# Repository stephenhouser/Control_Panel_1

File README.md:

# Control Panel

The old-school hard-switch control panel for Home Automation.

This project has a few parts, each documented in their own section below.

- Project Box from Amazon; link and description
- Base and Top panels; SVG files for a laser cutter
- PCBs for Base and Top panels; KiCad PCB designs for manufacture

# Project Box

The project box is a [BUD Industries PC-11495 Plastic Style F Box 9" W x 5" H x 8.5" D, Natural](
https://www.amazon.com/gp/product/B005T98PQS/ref=ppx_yo_dt_b_search_asin_title?ie=UTF8&psc=1) which I found on Amazon for ~$32 USD. The [Dimensions](https://www.budind.com/wp-content/uploads/2019/01/hb11495.pdf) are available from BUD Industries (thank you!)

Another option, without the top display is the [BUD Industries PC-11493 Plastic Style F Box 9" L x 8.5" W x 1.98" H, Natural](https://www.amazon.com/gp/product/B005T592P0/ref=ppx_yo_dt_b_search_asin_title?ie=UTF8&psc=1) for ~$30 USD. The [Dimensions](https://www.budind.com/wp-content/uploads/2019/01/hb11493.pdf) are available from BUD Industries (thank you!)

You can find details on these boxes in general from [BUD Industries](https://www.budind.com/series/general-use-boxes/plasticase-style-f-plastic-cases-2/#group=series-products&external_dimensions_group=0&internal_dimensions=0)

# Base and Top Panels

Look in the Box_Panels directory. These are SVG files for a laser cutter

# PCBs for Base and Top panels

Uses KiCad v7.x for two PCB's; Control Board and Display Board.

Control Board
---

- Version 1.0 sent to fab on 7/17/2023

Components:

-  1 x ESP32 DevKit C ([Amazon](https://www.amazon.com/AITRIP-ESP32-DevKitC-Development-ESP32-WROOM-32D-Compatible/dp/B08HMJ1X6W/ref=sr_1_1_sspa?crid=38RBRSP8DY486&keywords=esp32+devkitc&qid=1689705861&sprefix=esp32+devkit+%2Caps%2C108&sr=8-1-spons&sp_csd=d2lkZ2V0TmFtZT1zcF9hdGY&psc=1))
- 16 x Addressable RGB LEDs ([sparkfun](https://www.sparkfun.com/products/12986))
- 10 x 2-position SPST Toggle Switches ([Amazon](https://www.amazon.com/MTS-101-Position-Miniature-Toggle-Switch/dp/B0799LBFNY/ref=sr_1_1_sspa?crid=Q083CMZJXX9C&keywords=mini+toggle+switch&qid=1689705831&sprefix=mini+toggle+switch%2Caps%2C114&sr=8-1-spons&sp_csd=d2lkZ2V0TmFtZT1zcF9hdGY&psc=1))
-  1 x 3-position SPST Toggle Switch ([Amazon](https://www.amazon.com/Twidec-Momentary-Miniature-Waterproof-MTS-123-MZ/dp/B07VHCB1Q4/ref=sr_1_4?crid=1ODFBUY13M4Y&keywords=3+position+mini+toggle+switch&qid=1689705803&sprefix=3+position+mini+toggle+switch%2Caps%2C120&sr=8-4))
- 10 x 1N4148 Diodes
-  1 x Rotary Encoder + Knob ([Amazon](https://www.amazon.com/gp/product/B07DM2YMT4/ref=ppx_yo_dt_b_search_asin_title?ie=UTF8&psc=1))
-  1 x Mini pushbutton switch ([Amazon](https://www.amazon.com/Momentary-Spring-Return-Self-Return-Pushbutton-Switches/dp/B09DJY5Y5L/ref=sr_1_3?keywords=mini+pushbutton+switch&qid=1689705893&sprefix=mini+pushbutton+s%2Caps%2C102&sr=8-3))

)
)

Display Board
---
Display Board not yet created.

Components:

-  2 x 0.56" LED Display Digital Tube Clock Module 4 Digit ([Amazon](https://www.amazon.com/gp/product/B0BB72R6RW/ref=ppx_yo_dt_b_asin_title_o03_s00?ie=UTF8&psc=1))

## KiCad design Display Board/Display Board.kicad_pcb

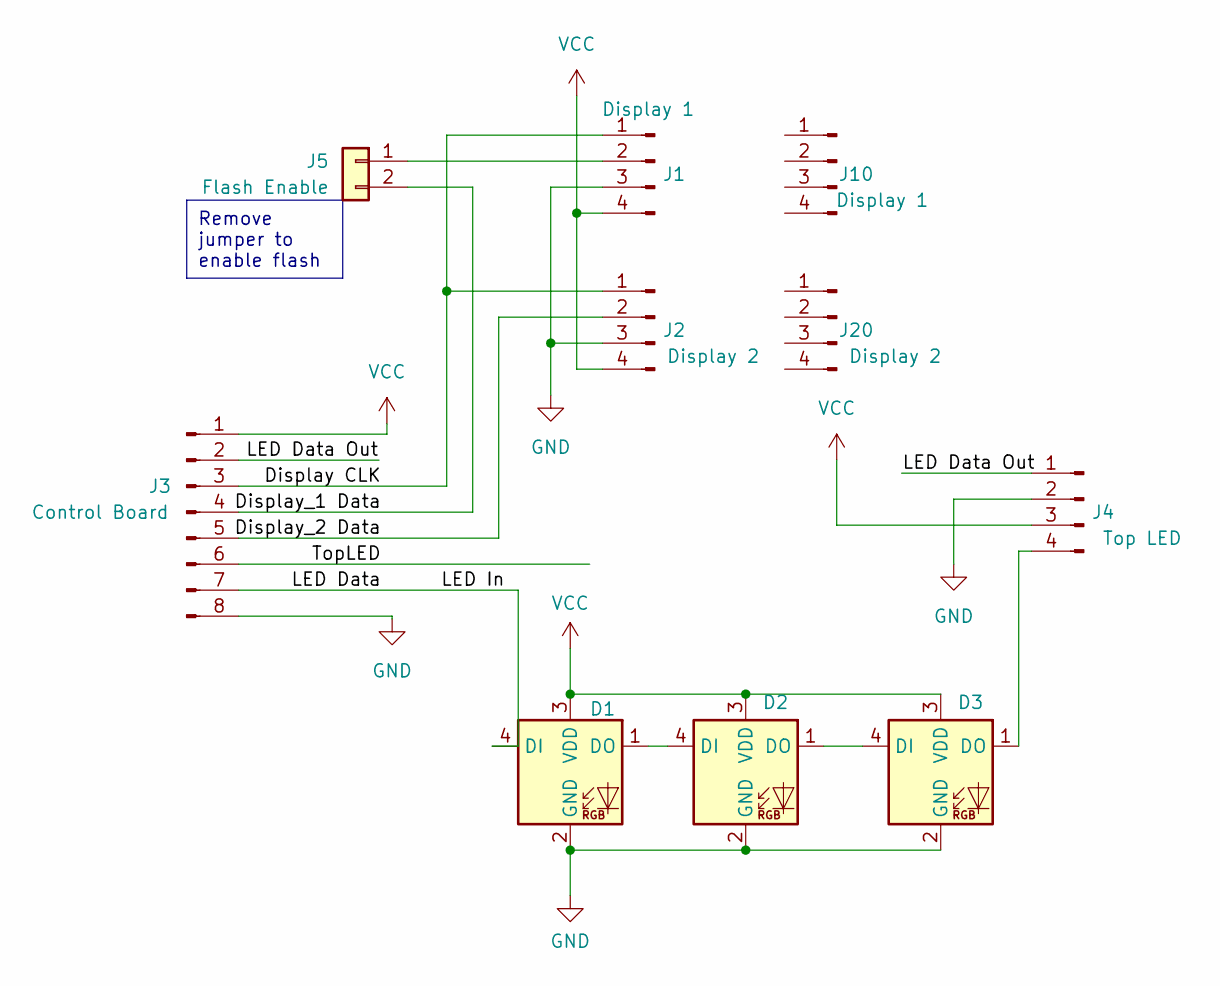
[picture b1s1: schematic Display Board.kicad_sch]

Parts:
D1, D2, D3: APA-106-F5; LED_D5.0mm-4_RGB
J1, J10: Display 1; PinHeader_1x04_P2.54mm_Vertical
J2, J20: Display 2; PinHeader_1x04_P2.54mm_Vertical
J3: Control Board; PinHeader_1x08_P2.00mm_Vertical
J4: Top LED; PinHeader_1x04_P2.00mm_Vertical
J5: Flash Enable; PinHeader_1x02_P2.54mm_Vertical

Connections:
/Display CLK: J1.1, J2.1, J3.3
/Display_1 Data: J3.4, J5.2
/Display_2 Data: J2.2, J3.5
/LED Data: D1.4 (DI), J3.7
/LED Data Out: J3.2, J4.1
/TopLED: J3.6
GND: D1.2 (GND), D2.2 (GND), D3.2 (GND), J1.3, J2.3, J3.8, J4.2
unnamed: D1.1 (DO), D2.4 (DI)
unnamed: D2.1 (DO), D3.4 (DI)
unnamed: D3.1 (DO), J4.4
unnamed: J1.2, J5.1
VCC: D1.3 (VDD), D2.3 (VDD), D3.3 (VDD), J1.4, J2.4, J3.1, J4.3

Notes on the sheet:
Remove jumper to enable flash

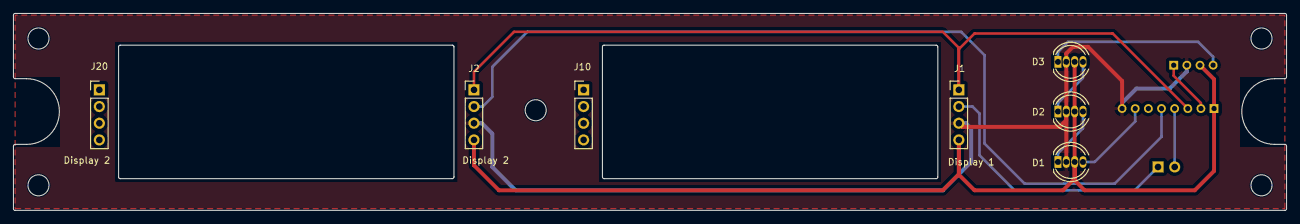
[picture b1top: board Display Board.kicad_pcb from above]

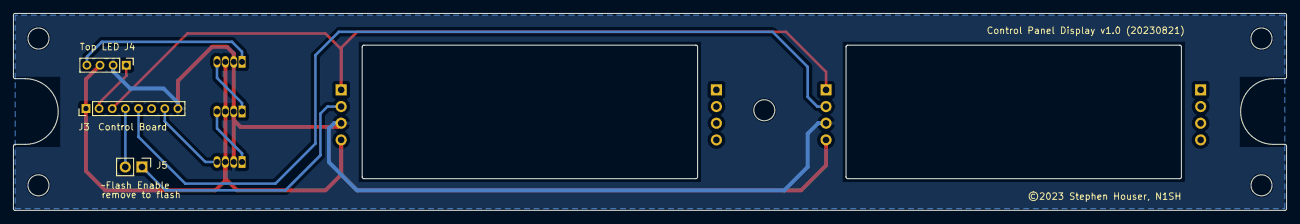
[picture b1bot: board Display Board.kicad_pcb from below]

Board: 2 copper layers, 193.8 x 30.0 mm, 15 parts (3 on the bottom side), 11 nets.

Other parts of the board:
REF01, REF02, REF03, REF04, REF05: MountingHole_3.2mm_M3

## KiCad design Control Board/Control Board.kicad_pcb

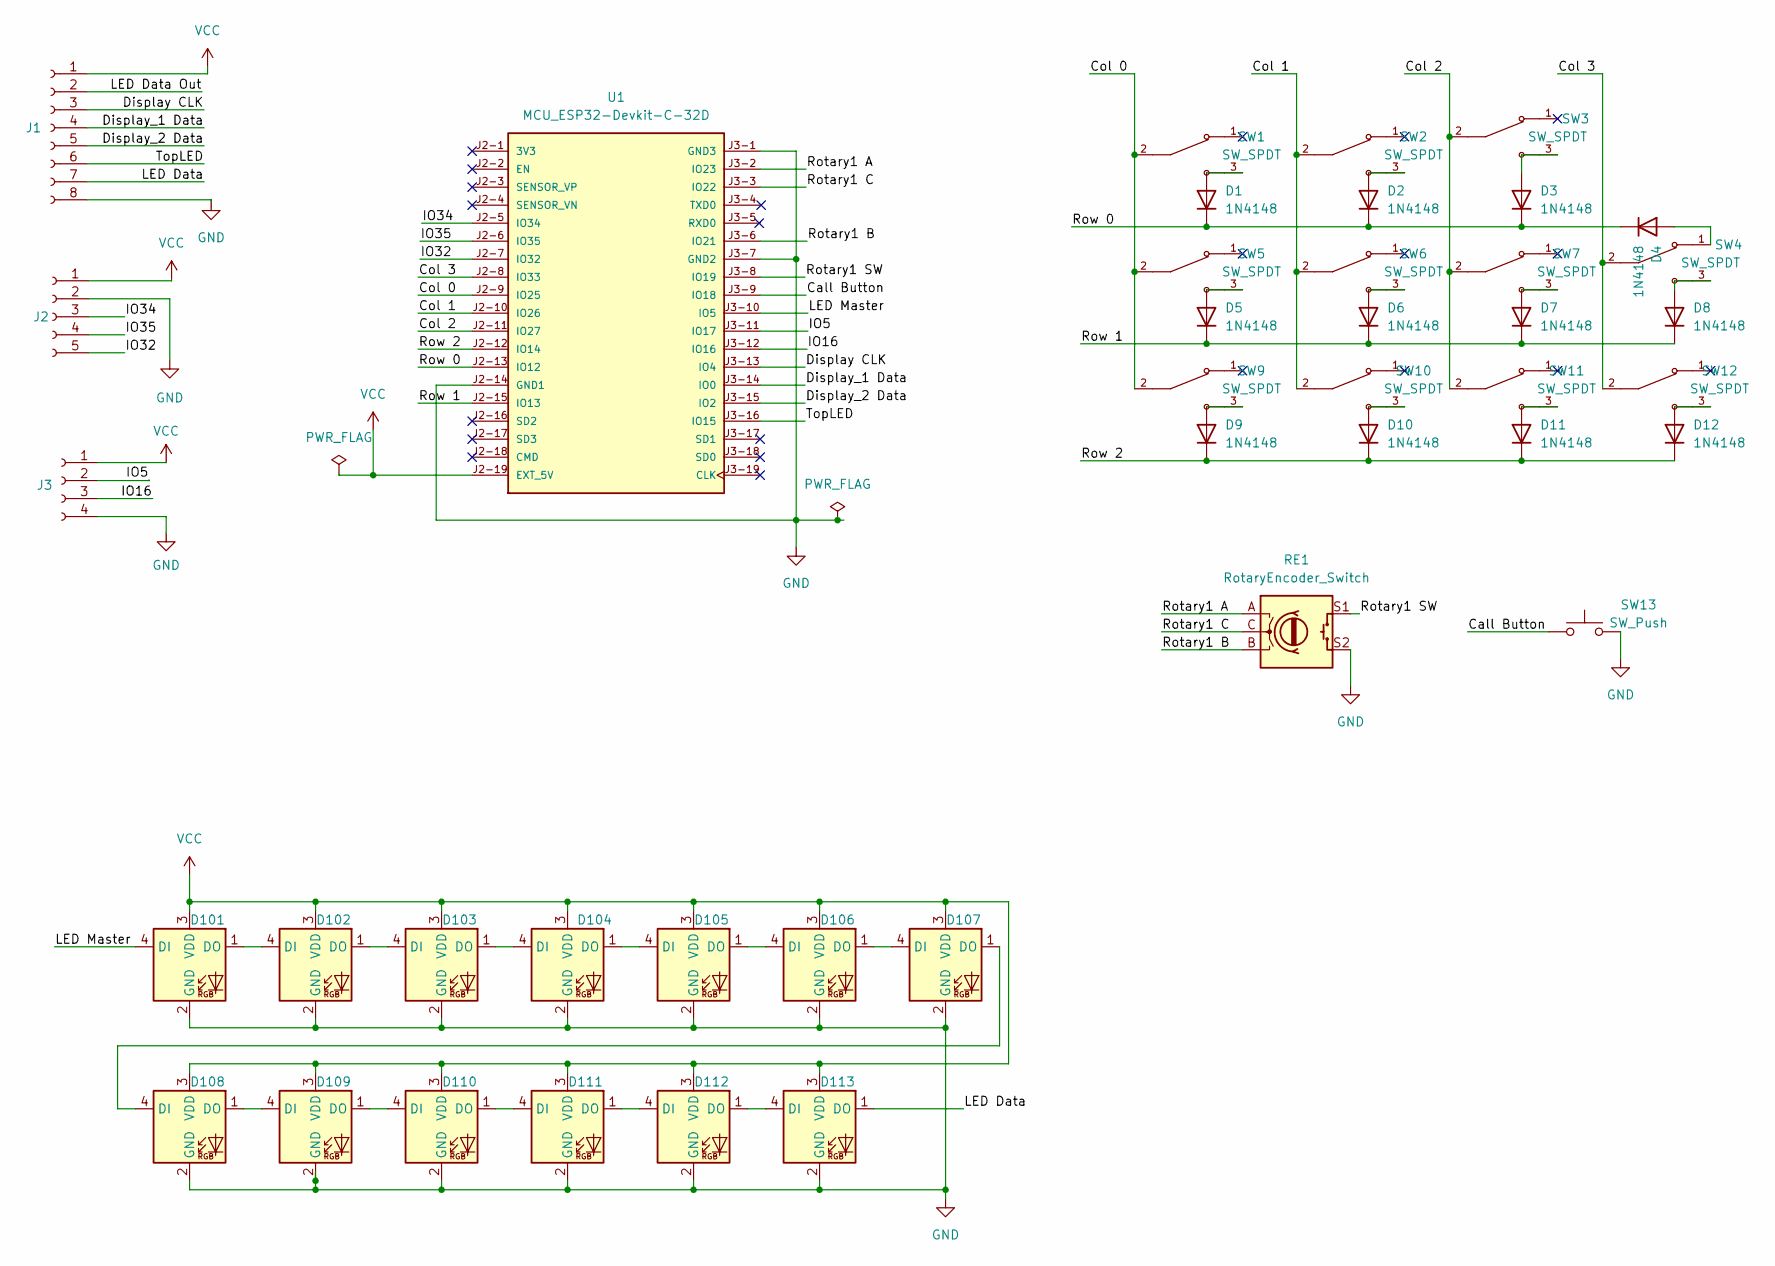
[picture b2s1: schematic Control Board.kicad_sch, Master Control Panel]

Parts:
D1, D2, D3, D4, D5, D6, D7, D8, D9, D10, D11, D12: 1N4148; D_DO-35_SOD27_P7.62mm_Horizontal
D101, D102, D103, D104, D105, D106, D107, D108, D109, D110, D111, D112, D113: APA-106-F5; LED_D5.0mm-4_RGB
J1: Conn_01x08_Socket; PinHeader_1x08_P2.00mm_Vertical
J2: Conn_01x05_Socket; PinHeader_1x05_P2.00mm_Vertical
J3: Conn_01x04_Socket; PinHeader_1x04_P2.00mm_Vertical
RE1: RotaryEncoder_Switch; RotaryEncoder_Alps_EC11E-Switch_Vertical_H20mm
SW1, SW2: SW_SPDT; SW_Mini_Toggle_100SP1T1B4M2QE; PARTREV E
SW3, SW4, SW5, SW6, SW7, SW9, SW10, SW11, SW12: SW_SPDT; SW_TOGGLE_100SP1T1B4M2QE; PARTREV E
SW13: SW_Push; SW_Mini_Pushbutton_PS1024ALRED
U1: MCU_ESP32-Devkit-C-32D; PARTREV V4

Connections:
/Call Button: SW13.1, U1.J3-9 (IO18)
/Col 0: SW1.2, SW5.2, SW9.2, U1.J2-9 (IO25)
/Col 1: SW2.2, SW6.2, SW10.2, U1.J2-10 (IO26)
/Col 2: SW3.2, SW7.2, SW11.2, U1.J2-11 (IO27)
/Col 3: SW4.2, SW12.2, U1.J2-8 (IO33)
/Display CLK: J1.3, U1.J3-13 (IO4)
/Display_1 Data: J1.4, U1.J3-14 (IO0)
/Display_2 Data: J1.5, U1.J3-15 (IO2)
/IO5: J3.2, U1.J3-11 (IO17)
/IO16: J3.3, U1.J3-12 (IO16)
/IO32: J2.5, U1.J2-7 (IO32)
/IO34: J2.3, U1.J2-5 (IO34)
/IO35: J2.4, U1.J2-6 (IO35)
/LED Data: D113.1 (DO), J1.7
/LED Data Out: J1.2
/LED Master: D101.4 (DI), U1.J3-10 (IO5)
/Rotary1 A: RE1.A, U1.J3-2 (IO23)
/Rotary1 B: RE1.B, U1.J3-6 (IO21)
/Rotary1 C: RE1.C, U1.J3-3 (IO22)
/Rotary1 SW: RE1.S1, U1.J3-8 (IO19)
/Row 0: D1.1 (K), D2.1 (K), D3.1 (K), D4.1 (K), U1.J2-13 (IO12)
/Row 1: D5.1 (K), D6.1 (K), D7.1 (K), D8.1 (K), U1.J2-15 (IO13)
/Row 2: D9.1 (K), D10.1 (K), D11.1 (K), D12.1 (K), U1.J2-12 (IO14)
/TopLED: J1.6, U1.J3-16 (IO15)
GND: D101.2 (GND), D102.2 (GND), D103.2 (GND), D104.2 (GND), D105.2 (GND), D106.2 (GND), D107.2 (GND), D108.2 (GND), D109.2 (GND), D110.2 (GND), D111.2 (GND), D112.2 (GND), D113.2 (GND), J1.8, J2.2, J3.4, RE1.S2, SW13.2, U1.J2-14 (GND1), U1.J3-1 (GND3), U1.J3-7 (GND2)
unnamed: D1.2 (A), SW1.3
unnamed: D2.2 (A), SW2.3
unnamed: D3.2 (A), SW3.3
unnamed: D4.2 (A), SW4.1
unnamed: D5.2 (A), SW5.3
unnamed: D6.2 (A), SW6.3
unnamed: D7.2 (A), SW7.3
unnamed: D8.2 (A), SW4.3
unnamed: D9.2 (A), SW9.3
unnamed: D10.2 (A), SW10.3
unnamed: D11.2 (A), SW11.3
unnamed: D12.2 (A), SW12.3
unnamed: D101.1 (DO), D102.4 (DI)
unnamed: D102.1 (DO), D103.4 (DI)
unnamed: D103.1 (DO), D104.4 (DI)
unnamed: D104.1 (DO), D105.4 (DI)
unnamed: D105.1 (DO), D106.4 (DI)
unnamed: D106.1 (DO), D107.4 (DI)
unnamed: D107.1 (DO), D108.4 (DI)
unnamed: D108.1 (DO), D109.4 (DI)
unnamed: D109.1 (DO), D110.4 (DI)
unnamed: D110.1 (DO), D111.4 (DI)
unnamed: D111.1 (DO), D112.4 (DI)
unnamed: D112.1 (DO), D113.4 (DI)
VCC: D101.3 (VDD), D102.3 (VDD), D103.3 (VDD), D104.3 (VDD), D105.3 (VDD), D106.3 (VDD), D107.3 (VDD), D108.3 (VDD), D109.3 (VDD), D110.3 (VDD), D111.3 (VDD), D112.3 (VDD), D113.3 (VDD), J1.1, J2.1, J3.1, U1.J2-19 (EXT_5V)

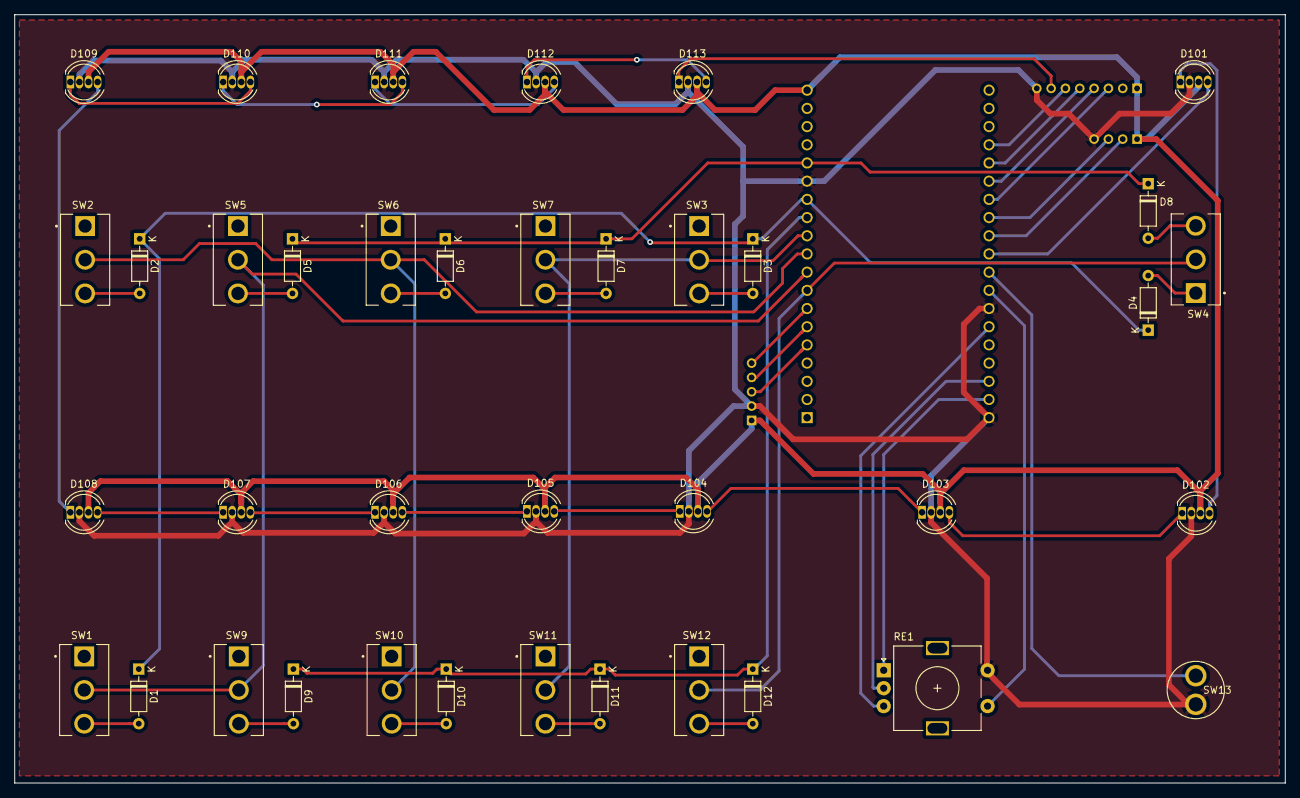
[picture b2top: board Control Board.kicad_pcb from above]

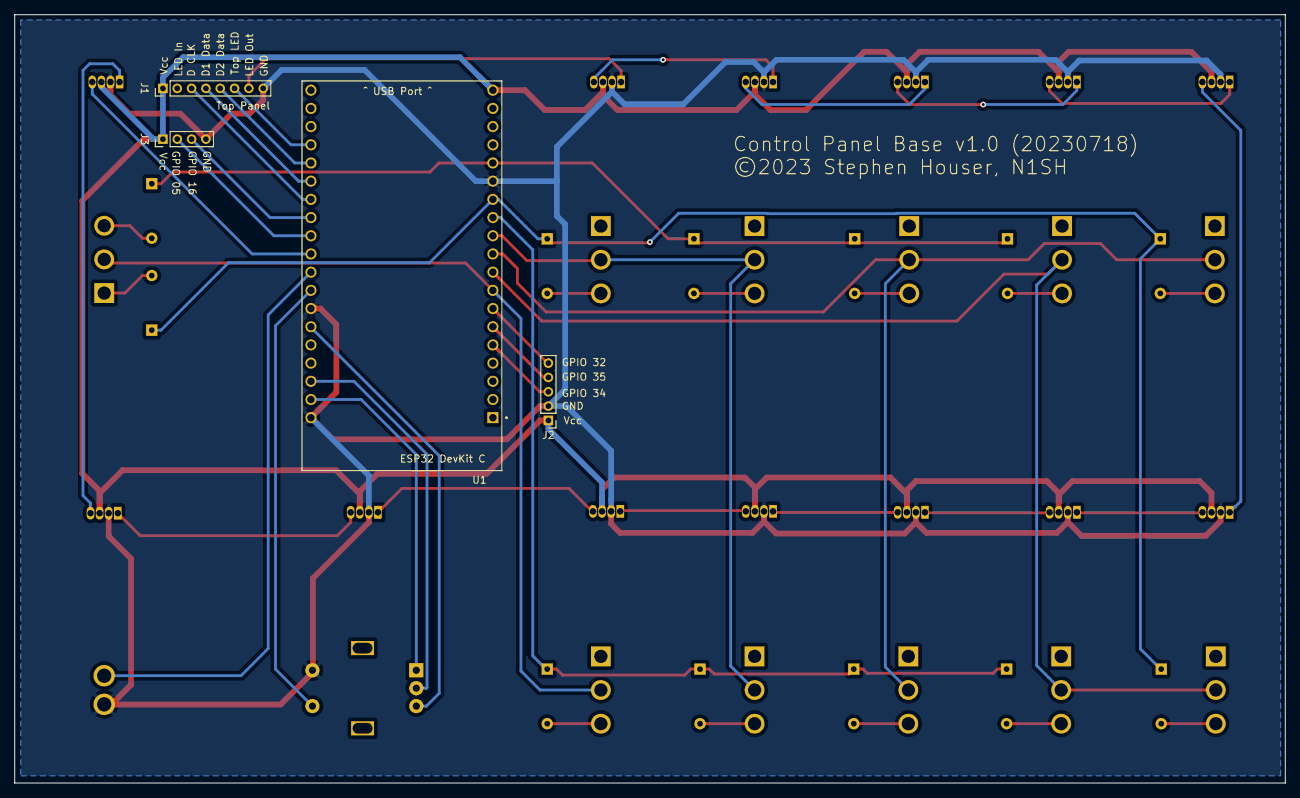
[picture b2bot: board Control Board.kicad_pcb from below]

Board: 2 copper layers, 177.4 x 107.3 mm, 42 parts (4 on the bottom side), 49 nets.

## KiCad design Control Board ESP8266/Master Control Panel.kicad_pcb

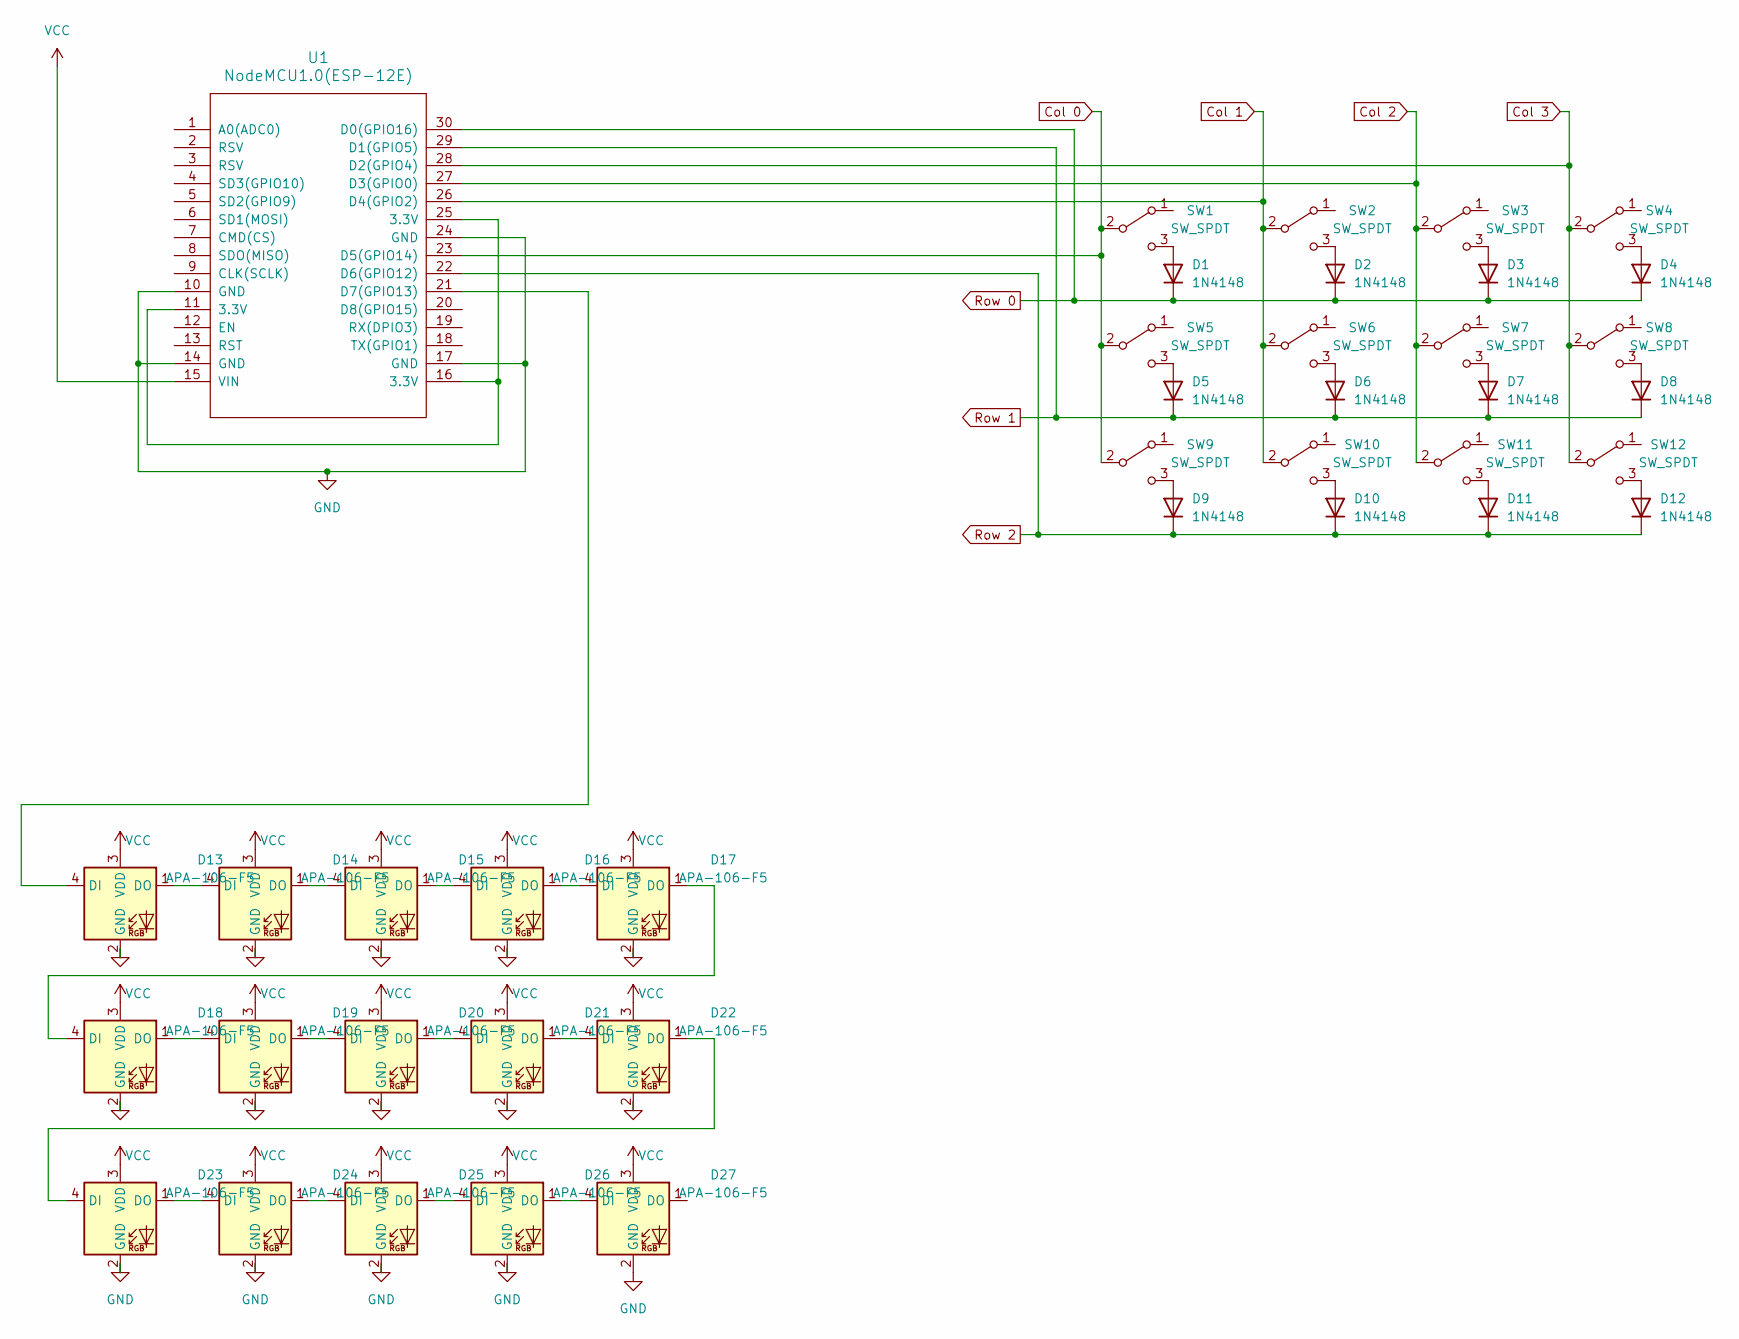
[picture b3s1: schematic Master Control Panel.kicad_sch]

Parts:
D1, D2, D3, D4, D5, D6, D7, D8, D9, D10, D11, D12: 1N4148; D_DO-35_SOD27_P7.62mm_Horizontal
D13, D14, D15, D16, D17, D18, D19, D20, D21, D22, D23, D24, D25, D26, D27: APA-106-F5; LED_D5.0mm-4_RGB
SW1, SW2, SW3, SW4, SW5, SW6, SW7, SW8, SW9, SW10, SW11, SW12: SW_SPDT; SW_100SP1T1B4M2QE
U1: NodeMCU1.0(ESP-12E); NodeMCU1.0(12-E)

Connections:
Col 0: SW1.2 (B), SW5.2 (B), SW9.2 (B), U1.23 (D5(GPIO14))
Col 1: SW2.2 (B), SW6.2 (B), SW10.2 (B), U1.26 (D4(GPIO2))
Col 2: SW3.2 (B), SW7.2 (B), SW11.2 (B), U1.27 (D3(GPIO0))
Col 3: SW4.2 (B), SW8.2 (B), SW12.2 (B), U1.28 (D2(GPIO4))
GND: D13.2 (GND), D14.2 (GND), D15.2 (GND), D16.2 (GND), D17.2 (GND), D18.2 (GND), D19.2 (GND), D20.2 (GND), D21.2 (GND), D22.2 (GND), D23.2 (GND), D24.2 (GND), D25.2 (GND), D26.2 (GND), D27.2 (GND), U1.10 (GND), U1.14 (GND), U1.17 (GND), U1.24 (GND)
unnamed: D1.2 (A), SW1.3 (C)
unnamed: D2.2 (A), SW2.3 (C)
unnamed: D3.2 (A), SW3.3 (C)
unnamed: D4.2 (A), SW4.3 (C)
unnamed: D5.2 (A), SW5.3 (C)
unnamed: D6.2 (A), SW6.3 (C)
unnamed: D7.2 (A), SW7.3 (C)
unnamed: D8.2 (A), SW8.3 (C)
unnamed: D9.2 (A), SW9.3 (C)
unnamed: D10.2 (A), SW10.3 (C)
unnamed: D11.2 (A), SW11.3 (C)
unnamed: D12.2 (A), SW12.3 (C)
unnamed: D13.4 (DI), U1.21 (D7(GPIO13))
unnamed: D13.1 (DO), D14.4 (DI)
unnamed: D14.1 (DO), D15.4 (DI)
unnamed: D15.1 (DO), D16.4 (DI)
unnamed: D16.1 (DO), D17.4 (DI)
unnamed: D17.1 (DO), D18.4 (DI)
unnamed: D18.1 (DO), D19.4 (DI)
unnamed: D19.1 (DO), D20.4 (DI)
unnamed: D20.1 (DO), D21.4 (DI)
unnamed: D21.1 (DO), D22.4 (DI)
unnamed: D22.1 (DO), D23.4 (DI)
unnamed: D23.1 (DO), D24.4 (DI)
unnamed: D24.1 (DO), D25.4 (DI)
unnamed: D25.1 (DO), D26.4 (DI)
unnamed: D26.1 (DO), D27.4 (DI)
unnamed: U1.11 (3.3V), U1.16 (3.3V), U1.25 (3.3V)
Row 0: D1.1 (K), D2.1 (K), D3.1 (K), D4.1 (K), U1.30 (D0(GPIO16))
Row 1: D5.1 (K), D6.1 (K), D7.1 (K), D8.1 (K), U1.29 (D1(GPIO5))
Row 2: D9.1 (K), D10.1 (K), D11.1 (K), D12.1 (K), U1.22 (D6(GPIO12))
VCC: D13.3 (VDD), D14.3 (VDD), D15.3 (VDD), D16.3 (VDD), D17.3 (VDD), D18.3 (VDD), D19.3 (VDD), D20.3 (VDD), D21.3 (VDD), D22.3 (VDD), D23.3 (VDD), D24.3 (VDD), D25.3 (VDD), D26.3 (VDD), D27.3 (VDD), U1.15 (VIN)

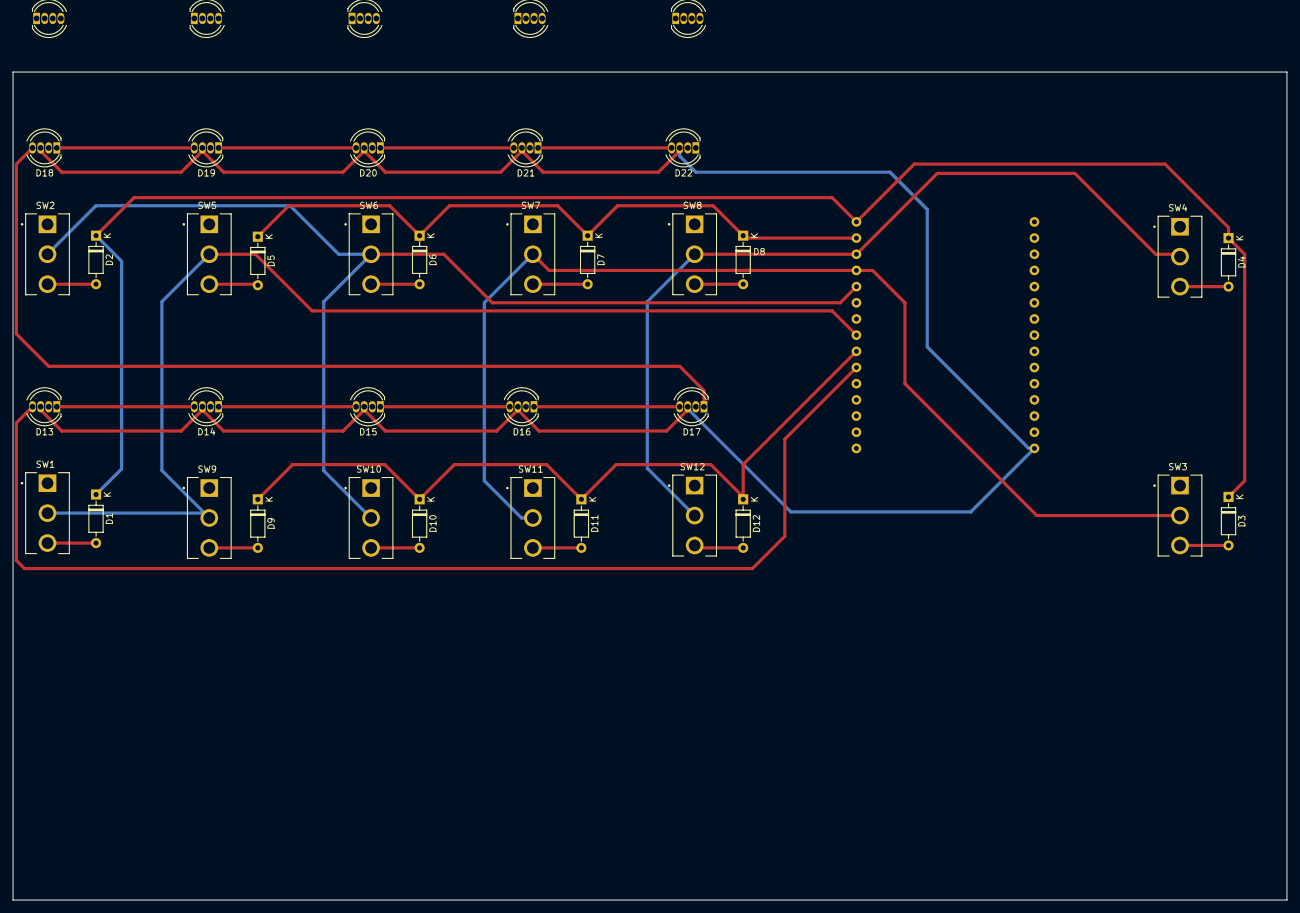
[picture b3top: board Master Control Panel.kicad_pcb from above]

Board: 2 copper layers, 200.0 x 130.0 mm, 40 parts (1 on the bottom side), 37 nets.

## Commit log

2023-07-18 remove old svg files
2023-07-18 add details on project boxes
2023-07-18 add product links to readme
2023-07-19 rename to control board
2023-07-19 add initial display board
2023-07-20 update display board
2023-07-24 add panel test, platformio code
2023-07-28 esphome external component
2023-07-28 clean up old Master version
2023-07-28 add led to keyboard
2023-07-30 add images, remove python cache
2023-07-30 remove python cache files
2023-07-30 add leds and some samples
2023-07-31 add blueprints for easier config
2023-07-31 update blueprints
2023-07-31 remove partial blueprints
2023-07-31 clean up working files
2023-08-01 add sample automation
2023-08-01 update blueprint
2023-08-13 update with more testing
2023-08-21 working on display board and mounting
2023-08-21 saved
2023-08-21 rename ESPHome
2023-08-21 rename esphome.new part2
2023-08-21 update readme, add qr codes
2023-08-21 update display board with mounting holes and copper pour
2023-08-21 re-route
2023-08-22 v1.0-20230821
2023-08-29 tweaking top led
2023-08-29 final build of v1
2023-09-10 add qrcode to stephenhouser.com
2023-09-10 add appdaemon and homeassistant portions
2023-09-10 fix file location

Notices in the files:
Control Board/Control Board.kicad_pcb:
©2023 Stephen Houser, N1SH
